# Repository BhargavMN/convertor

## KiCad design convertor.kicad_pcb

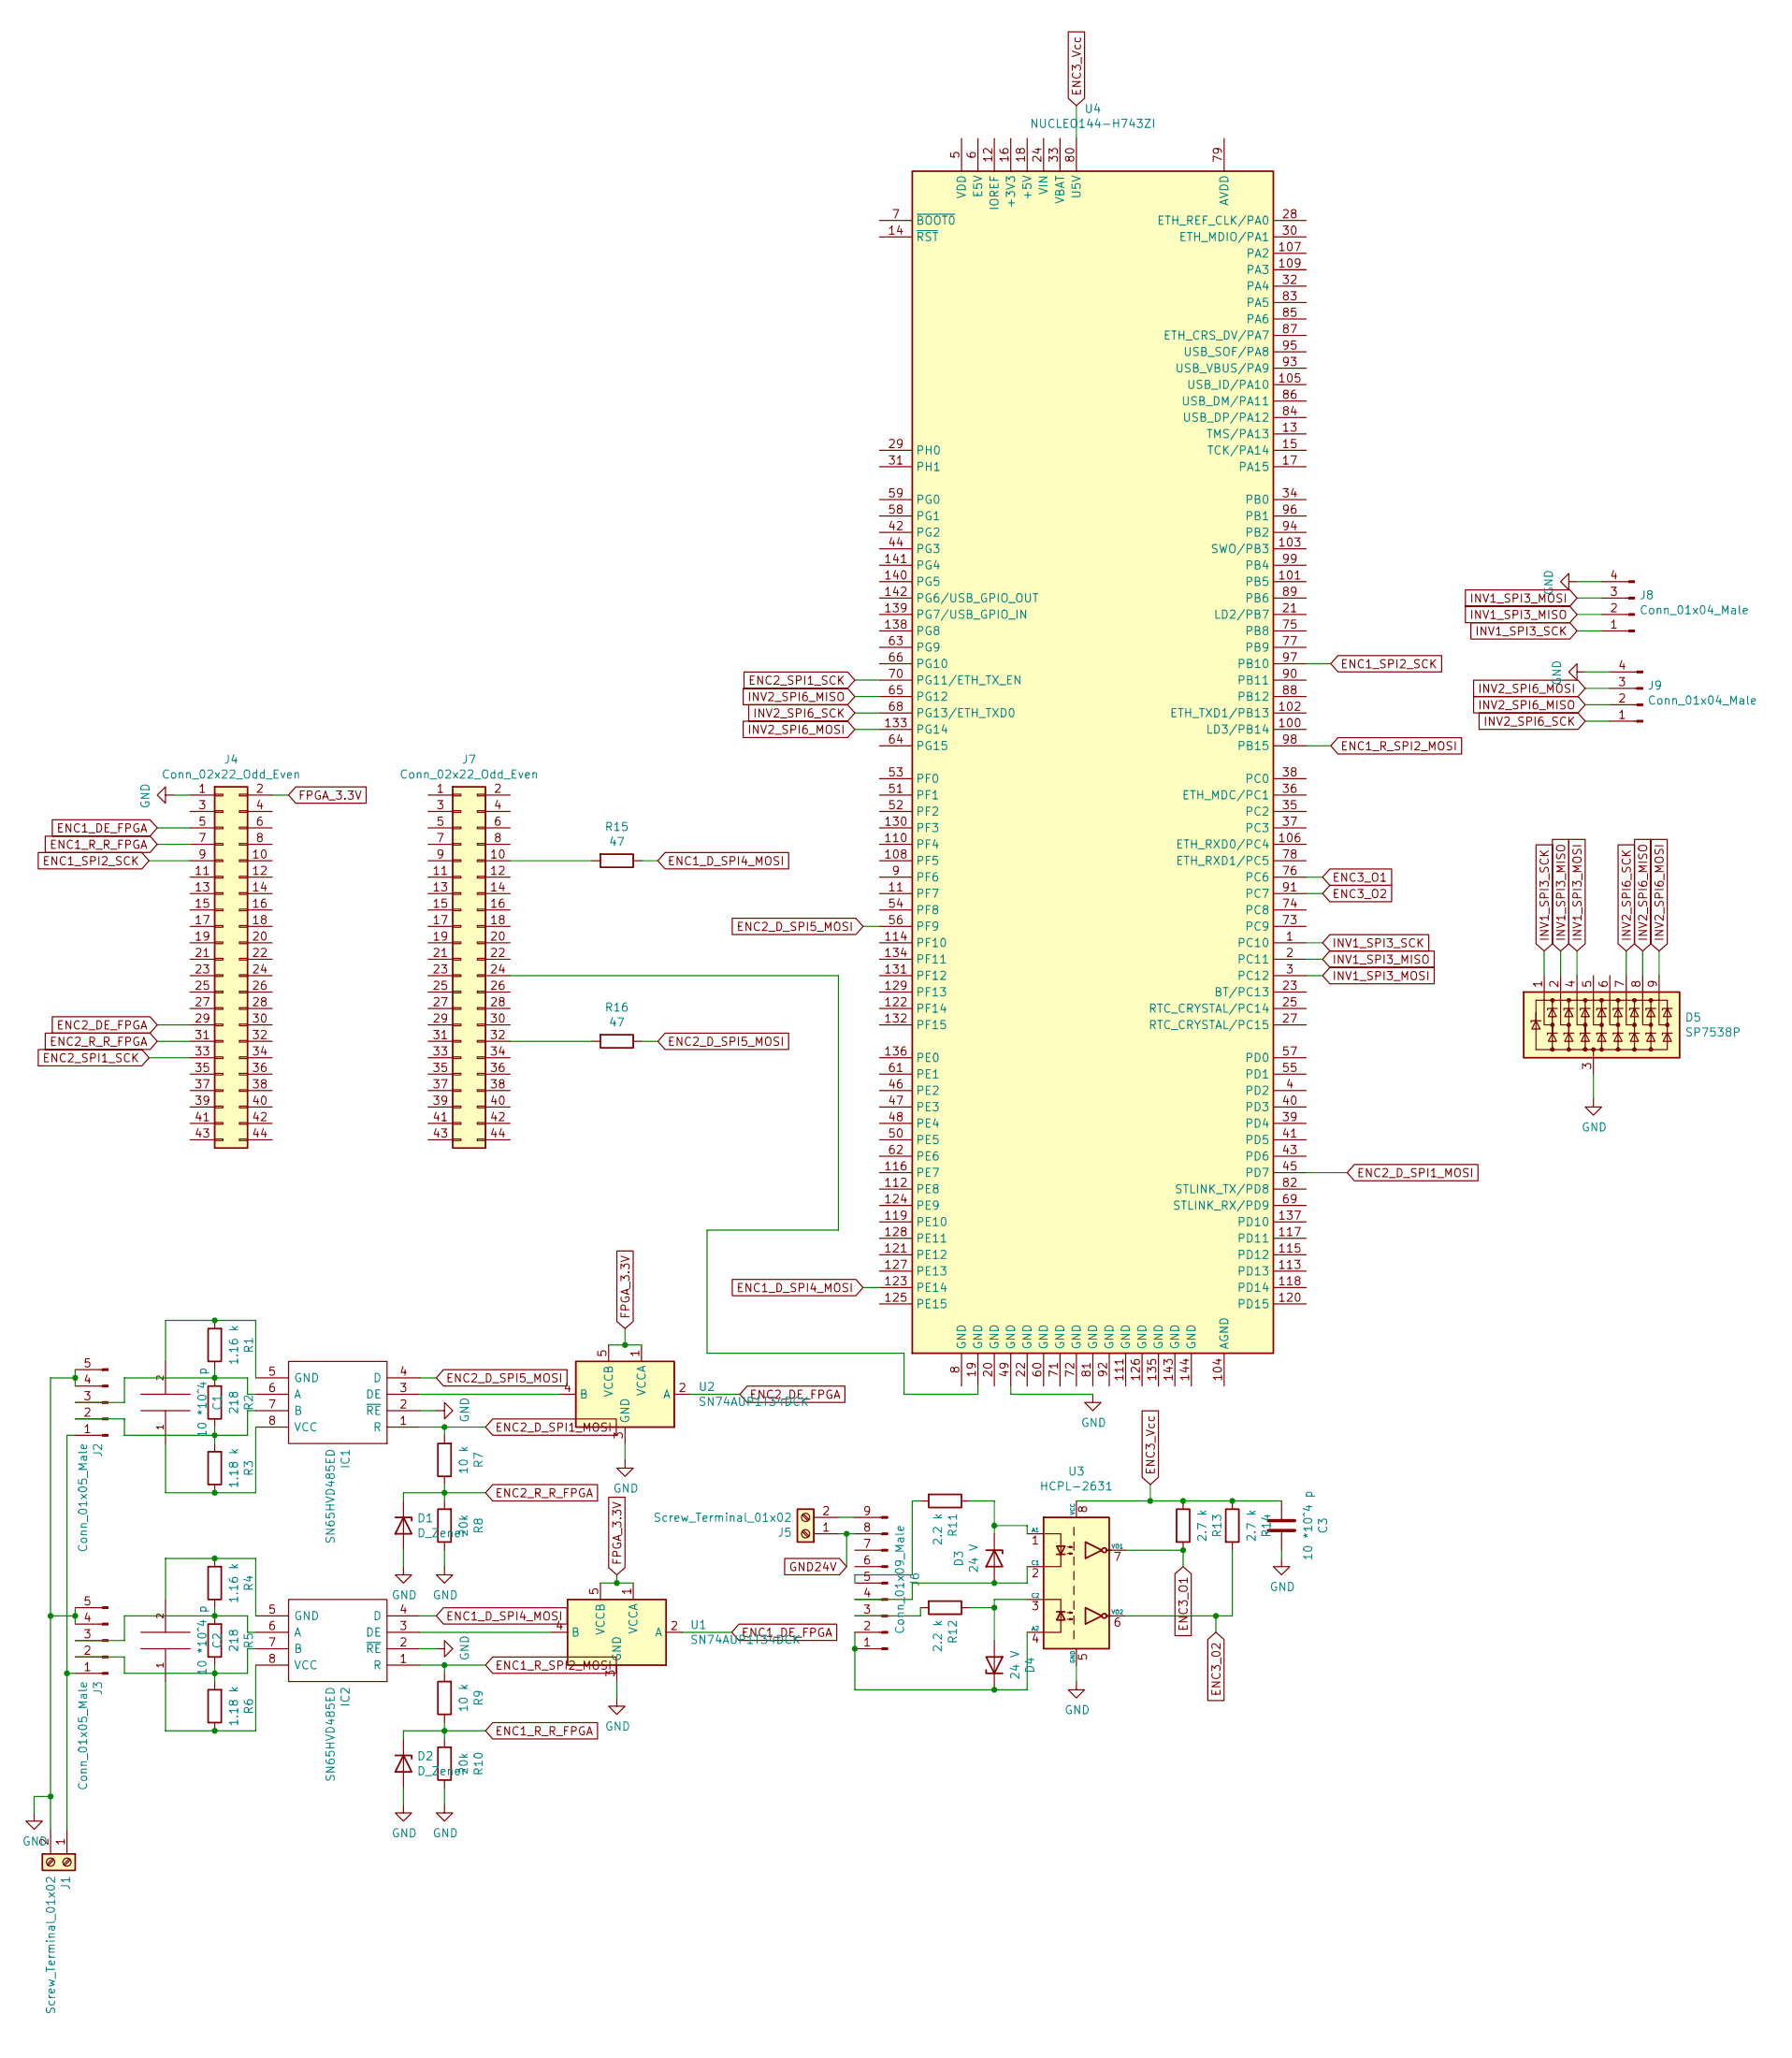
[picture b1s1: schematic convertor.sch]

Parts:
C1, C2, C3: 10 *10^4 p; C_0805_2012Metric
D1, D2: D_Zener; D_DO-35_SOD27_P7.62mm_Horizontal
D3, D4: 24 V; D_DO-35_SOD27_P7.62mm_Horizontal
D5: SP7538P; UDFN-9_1.0x3.8mm_P0.5mm
IC1, IC2: SN65HVD485ED; SOIC127P600X175-8N_THT; Manufacturer_Part_Number SN65HVD485ED; Mouser Part Number 595-SN65HVD485ED
J1, J5: Screw_Terminal_01x02; PhoenixContact_MCV_1,5_2-G-3.81_1x02_P3.81mm_Vertical
J2, J3: Conn_01x05_Male; PinHeader_1x05_P2.54mm_Vertical
J4, J7: Conn_02x22_Odd_Even; PinSocket_2x22_P2.54mm_Vertical
J6: Conn_01x09_Male; PinHeader_2x05_P2.54mm_Vertical
J8, J9: Conn_01x04_Male; PinHeader_1x04_P2.54mm_Vertical
R1, R4: 1.16 k; R_0805_2012Metric
R2, R5: 218; R_0805_2012Metric
R3, R6: 1.18 k; R_0805_2012Metric
R7, R9: 10 k; R_0805_2012Metric
R8, R10: 20k; R_0805_2012Metric
R11, R12: 2.2 k; R_Axial_DIN0309_L9.0mm_D3.2mm_P5.08mm_Vertical
R13, R14: 2.7 k; R_0805_2012Metric
R15, R16: 47; R_0805_2012Metric
U1, U2: SN74AUP1T34DCK; SOT-353_SC-70-5
U3: HCPL-2631; DIP-8_W7.62mm
U4: NUCLEO144-H743ZI; ST_Morpho_Connector_144_STLink

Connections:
ENC1_DE_FPGA: J4.5, U1.2 (A)
ENC1_D_SPI4_MOSI: IC2.4 (D), R15.1, U4.123 (PE14)
ENC1_R_R_FPGA: D2.1 (K), J4.7, R9.1, R10.2
ENC1_R_SPI2_MOSI: IC2.1 (R), R9.2, U4.98 (PB15)
ENC1_SPI2_SCK: J4.9, U4.97 (PB10)
ENC2_DE_FPGA: J4.29, U2.2 (A)
ENC2_D_SPI1_MOSI: IC1.1 (R), R7.2, U4.45 (PD7)
ENC2_D_SPI5_MOSI: IC1.4 (D), R16.1, U4.56 (PF9)
ENC2_R_R_FPGA: D1.1 (K), J4.31, R7.1, R8.2
ENC2_SPI1_SCK: J4.33, U4.70 (PG11/ETH_TX_EN)
ENC3_02: R14.2, U3.6 (VO2)
ENC3_O1: R13.2, U3.7 (VO1), U4.76 (PC6)
ENC3_O2: U4.91 (PC7)
ENC3_Vcc: C3.2, R13.1, R14.1, U3.8 (VCC), U4.80 (U5V)
FPGA_3.3V: J4.2, U1.1 (VCCA), U1.5 (VCCB), U2.1 (VCCA), U2.5 (VCCB)
GND: C3.1, D1.2 (A), D2.2 (A), D5.3 (A), IC1.2 (~RE), IC2.2 (~RE), J1.2, J2.4, J2.5, J3.4, J3.5, J4.1, J8.4, J9.4, R8.1, R10.1, U1.3 (GND), U2.3 (GND), U3.5 (GND), U4.49 (GND)
GND24V: J5.1, J6.8
INV1_SPI3_MISO: D5.2 (K2), J8.2, U4.2 (PC11)
INV1_SPI3_MOSI: D5.4 (K3), J8.3, U4.3 (PC12)
INV1_SPI3_SCK: D5.1 (K1), J8.1, U4.1 (PC10)
INV2_SPI6_MISO: D5.8 (K7), J9.2, U4.65 (PG12)
INV2_SPI6_MOSI: D5.9 (K8), J9.3, U4.133 (PG14)
INV2_SPI6_SCK: D5.7 (K6), J9.1, U4.68 (PG13/ETH_TXD0)
unnamed: C1.1, IC1.8 (VCC), R3.1
unnamed: C1.2, IC1.5 (GND), R1.2
unnamed: C2.1, IC2.8 (VCC), R6.1
unnamed: C2.2, IC2.5 (GND), R4.2
unnamed: D3.1 (K), R11.1, U3.1 (A1)
unnamed: D3.2 (A), J6.4, U3.2 (C1)
unnamed: D4.1 (K), J6.1, J6.2, U3.4 (A2)
unnamed: D4.2 (A), R12.1, U3.3 (C2)
unnamed: IC1.3 (DE), U2.4 (B)
unnamed: IC1.6 (A), J2.3, R1.1, R2.2
unnamed: IC1.7 (B), J2.2, R2.1, R3.2
unnamed: IC2.3 (DE), U1.4 (B)
unnamed: IC2.6 (A), J3.3, R4.1, R5.2
unnamed: IC2.7 (B), J3.2, R5.1, R6.2
unnamed: J1.1, J2.1, J3.1
unnamed: J5.2, J6.9
unnamed: J6.3, R12.2
unnamed: J6.5, R11.2
unnamed: J7.10, R15.2
unnamed: J7.24, U4.19 (GND)
unnamed: J7.32, R16.2

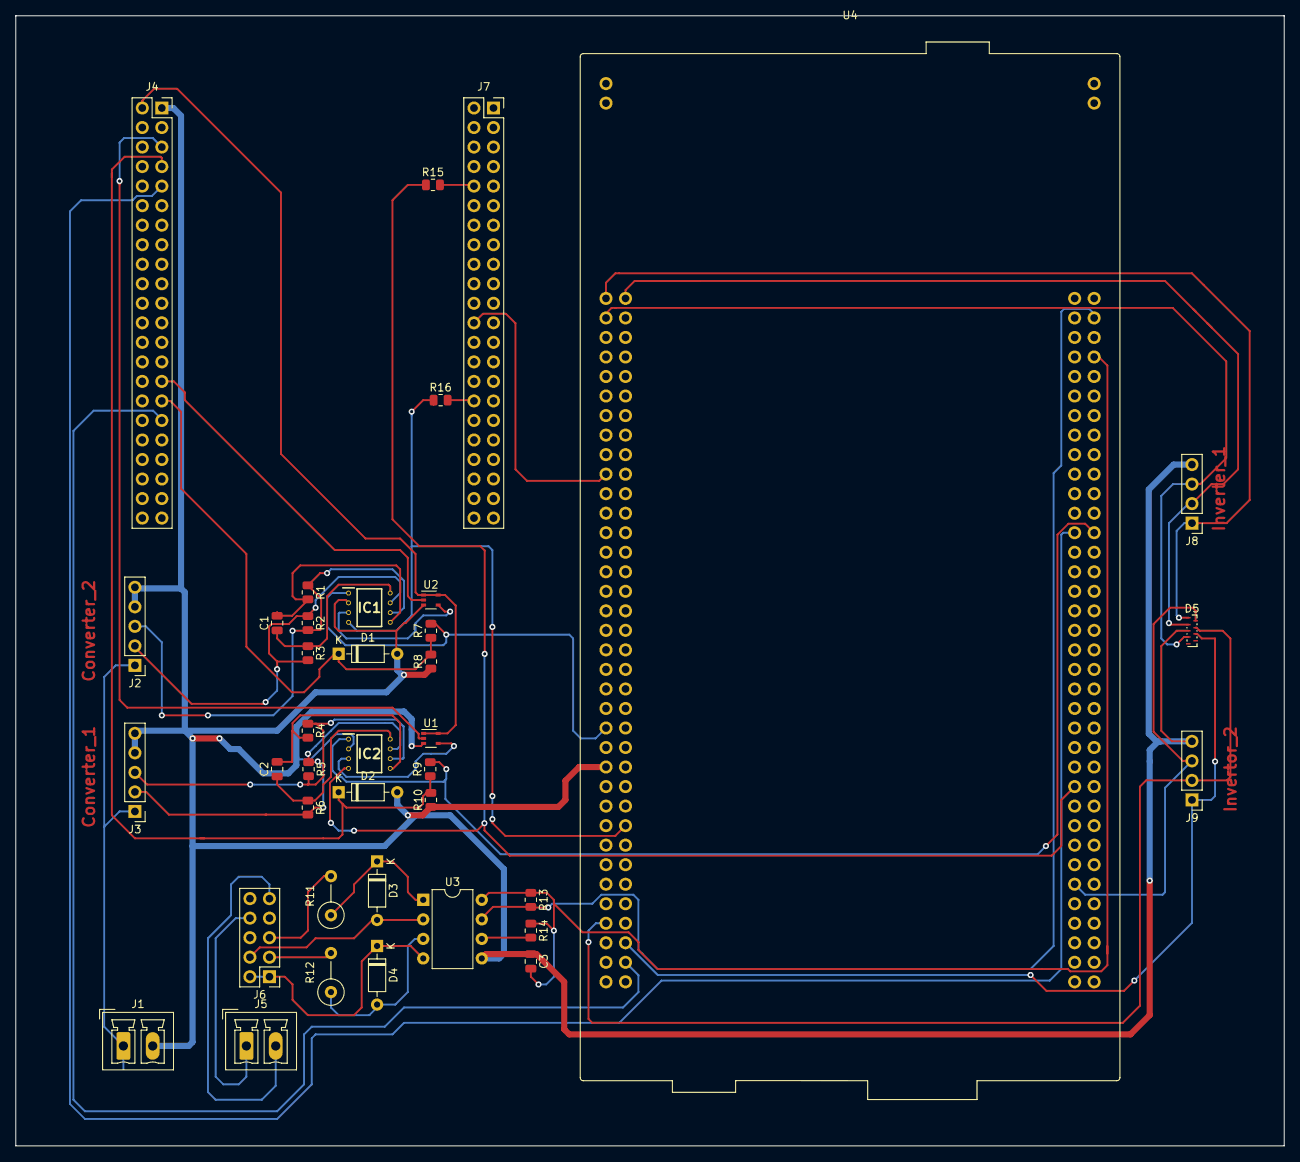
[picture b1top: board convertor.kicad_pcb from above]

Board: 2 copper layers, 165.0 x 147.0 mm, 39 parts (0 on the bottom side), 43 nets.

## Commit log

2022-05-13 Resources
